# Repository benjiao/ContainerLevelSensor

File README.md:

# Container Level Sensor
by Benjie Jiao

[![CC BY-SA 4.0][cc-by-sa-shield]][cc-by-sa]
[![ko-fi][ko-fi-badge]][ko-fi]

A DIY sensor for measuring the fill level of a container (e.g. our cat food bin),
based on an ESP32-C3 and a VL53L0x time-of-flight distance sensor, reporting
to Home Assistant over ESPHome.

For more info, check out the [build writeup][blog-post]. If this project was
useful to you, consider [buying me a coffee][ko-fi].

This is meant to be mounted under a container's lid. Like this prototype mounted to monitor our laundry basket.

## Repository contents

- `hardware/kicad/ContainerLevelSensor/` — KiCad project (schematic + PCB) for
  the sensor board. Open `ContainerLevelSensor.kicad_pro` in KiCad to view or
  edit the design.

- `hardware/kicad/Fabrication/` — Generated Gerber/drill files and a ready-to
  order `.zip`, for sending straight to a PCB fab (e.g. PCBWay).
- `hardware/openscad/ContainerLevelSensor.scad` — Parametric enclosure,
  generated with [YAPP_Box](hardware/openscad/YAPP_Box) (included as a git
  submodule — run `git submodule update --init --recursive` before opening
  the `.scad` file in OpenSCAD). `ContainerLevelSensor.stl` is the pre-rendered
  mesh, ready to send to a 3D slicer as-is.
- `hardware/old_revisions/` — Earlier hardware revisions, kept for reference.
- `software/esphome/container-level.yaml` — [ESPHome](https://esphome.io)
  firmware configuration for the ESP32-C3. See "Flashing the firmware" below.

## Flashing the firmware

1. In Home Assistant, install the [ESPHome add-on](https://esphome.io/guides/getting_started_hassio.html)
   from Settings → Add-ons → Add-on Store (search for "ESPHome"), then start it.
2. Open the ESPHome add-on's web UI (or the ESPHome dashboard panel in the
   sidebar) and add a new device, then replace its generated YAML with the
   contents of `software/esphome/container-level.yaml`.
3. The add-on manages Wi-Fi credentials and secrets for you — when prompted,
   enter your Wi-Fi SSID/password; these are stored in its own `secrets.yaml`.
4. Replace the placeholder `api.encryption.key` and `ota.password` values in
   the config with your own (the dashboard can generate these for you when
   creating the device).
5. Connect the ESP32-C3 board over USB to the machine running Home Assistant
   (or use "Wirelessly" for subsequent updates once initially flashed), then
   click **Install** in the ESPHome dashboard for that device.
6. Once flashed, the device auto-connects to Home Assistant via the ESPHome
   integration, exposing the raw `VL53L0x Distance` reading and a computed
   `Level` percentage.

The `Keep Awake Jumper` pin (GPIO3) holds the board awake for
reflashing/debugging; otherwise the board deep-sleeps between readings to
save battery. Adjust `bottom_distance` in the `Level` sensor's lambda to
match the distance (in meters) from the sensor to the bottom of your
container.

## License

This work is licensed under a
[Creative Commons Attribution-ShareAlike 4.0 International License][cc-by-sa].

[![CC BY-SA 4.0][cc-by-sa-image]][cc-by-sa]

[cc-by-sa]: http://creativecommons.org/licenses/by-sa/4.0/
[cc-by-sa-image]: https://licensebuttons.net/l/by-sa/4.0/88x31.png
[cc-by-sa-shield]: https://img.shields.io/badge/License-CC%20BY--SA%204.0-lightgrey.svg
[blog-post]: https://benjiao.net/posts/catfood-level-sensor/
[ko-fi]: https://ko-fi.com/benjiao
[ko-fi-badge]: https://img.shields.io/badge/ko--fi-support-ff5e5b?logo=ko-fi&logoColor=white

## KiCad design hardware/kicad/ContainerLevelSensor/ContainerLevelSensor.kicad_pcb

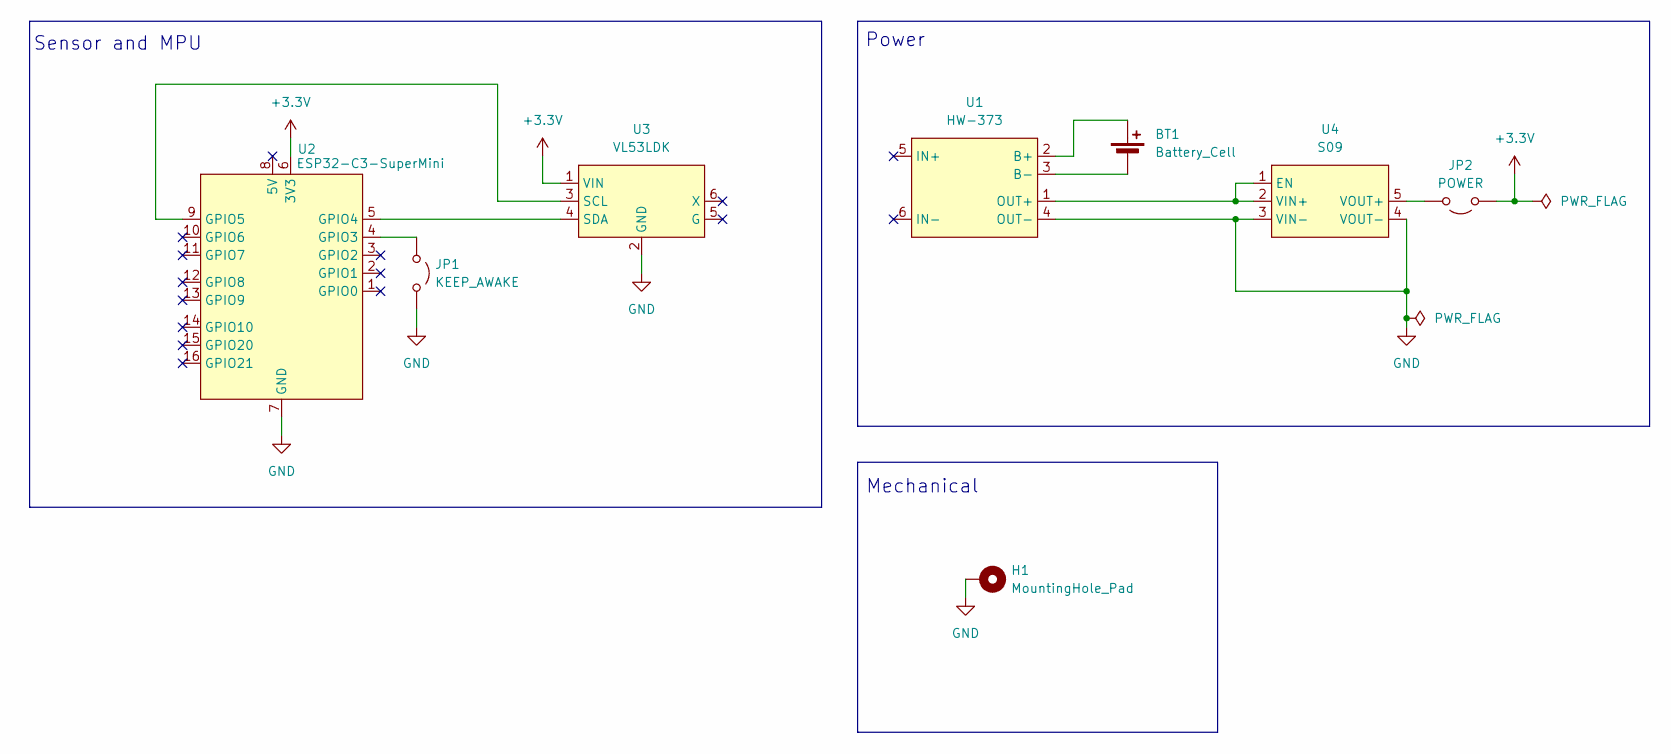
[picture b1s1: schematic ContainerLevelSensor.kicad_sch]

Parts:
BT1: Battery_Cell; BatteryHolder_MPD_BH-18650-PC
H1: MountingHole_Pad; MountingHole_3.2mm_M3_DIN965_Pad
JP1: KEEP_AWAKE; SW_DIP_SPSTx01_Slide_6.7x4.1mm_W7.62mm_P2.54mm_LowProfile
JP2: POWER; SW_DIP_SPSTx01_Slide_6.7x4.1mm_W7.62mm_P2.54mm_LowProfile
U1: HW-373; Module_HW-373_Li-Ion_Charging
U2: ESP32-C3-SuperMini; ESP32-C3-SuperMini_Edge
U3: VL53LDK; Module_VL53LDK_Distance_Sensor
U4: S09; Module_S09_DC_to_DC_Edge

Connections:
+3.3V: JP2.1 (A), U2.6 (3V3), U3.1 (VIN)
GND: H1.1, JP1.2 (B), U1.4 (OUT-), U2.7 (GND), U3.2 (GND), U4.3 (VIN-), U4.4 (VOUT-)
unnamed: BT1.1 (+), U1.2 (B+)
unnamed: BT1.2 (-), U1.3 (B-)
unnamed: JP1.1 (A), U2.4 (GPIO3)
unnamed: JP2.2 (B), U4.5 (VOUT+)
unnamed: U1.1 (OUT+), U4.1 (EN), U4.2 (VIN+)
unnamed: U2.5 (GPIO4), U3.4 (SDA)
unnamed: U2.9 (GPIO5), U3.3 (SCL)

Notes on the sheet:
Sensor and MPU
Power
Mechanical

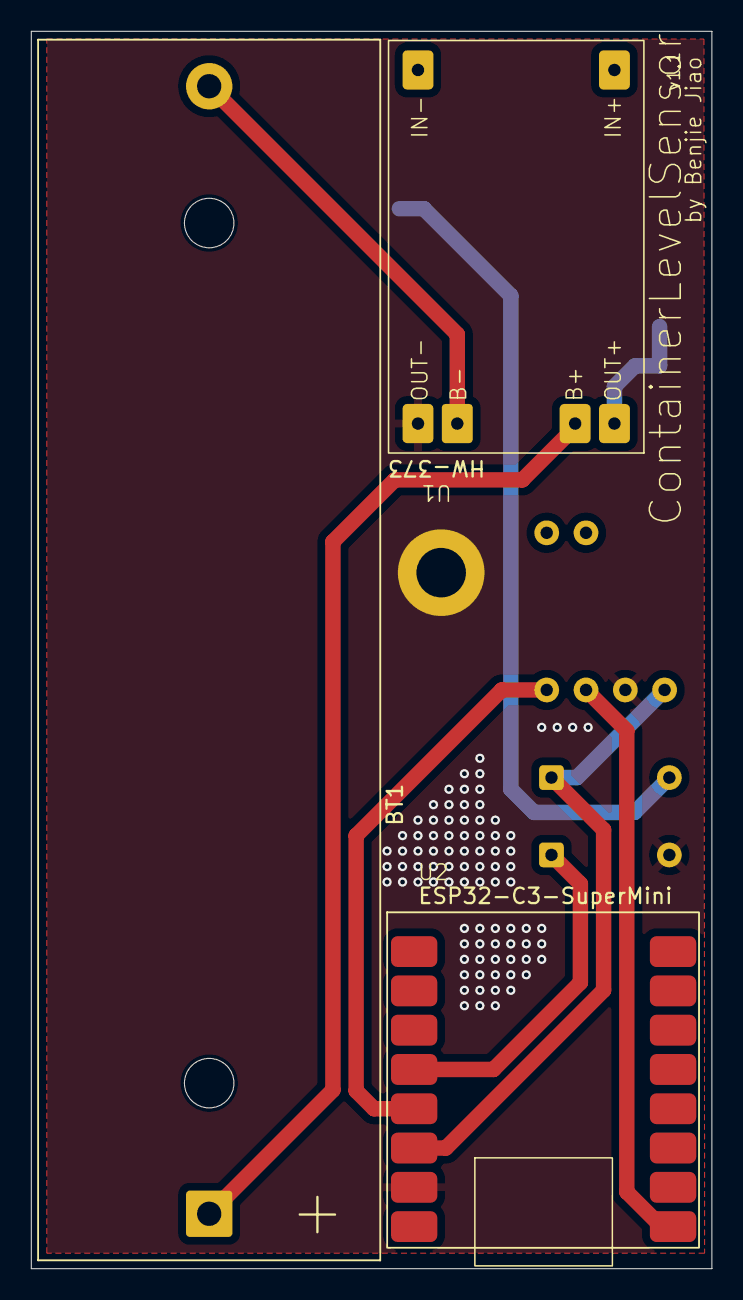
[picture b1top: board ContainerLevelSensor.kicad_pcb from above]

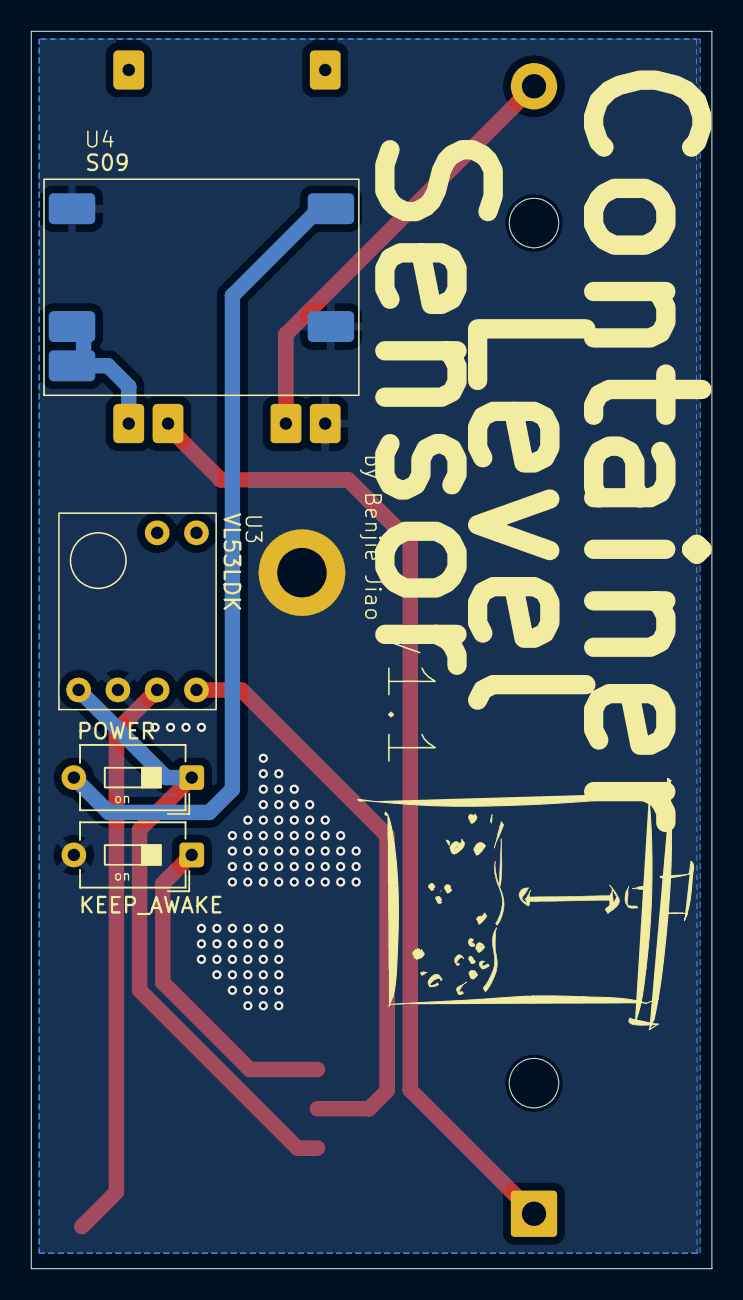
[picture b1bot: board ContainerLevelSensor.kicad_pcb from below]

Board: 2 copper layers, 44.0 x 80.0 mm, 8 parts (4 on the bottom side), 9 nets.

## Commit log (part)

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2026-02-26 added version 1 files
2026-02-26 Added readme and license
2026-02-26 cleanup
2026-02-26 Added software
2026-03-22 Added v1.1
2026-04-05 Added version 1.1
